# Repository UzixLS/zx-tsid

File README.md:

## ZX-TSid
MOS SID sound card for ZX Spectrum edge connector (ZX-BUS).

PCB is compatible with SID 6581 and 8580, but also contains integrated SwinSID emulator.

SID accessible via #xxCF port, where xx - SID's register number.

You may connect your ZX Spectrum audio output to second 3.5mm jack and it will be mixed in sound card output signal.

NOTE: +12V/+9V voltage is strictly required for SID, your ZX Spectrum or clone must provide it on the edge connector.

### Changelog & current status
* Rev.A - initial release with SID, AY and Covox. [Errata](pcb/rev.A/ERRATA.txt).
* Rev.B - abandoned. Files kept for historical reason.
* Rev.C - removed AY and Covox. Added SwinSID emulator. PCB is vertical oriented now.
* Rev.D - improved signal-noise ratio. Fixed read from SID chip.

TODO:
* Check with 8580 SID chip;
* Further improve signal-noise ratio.

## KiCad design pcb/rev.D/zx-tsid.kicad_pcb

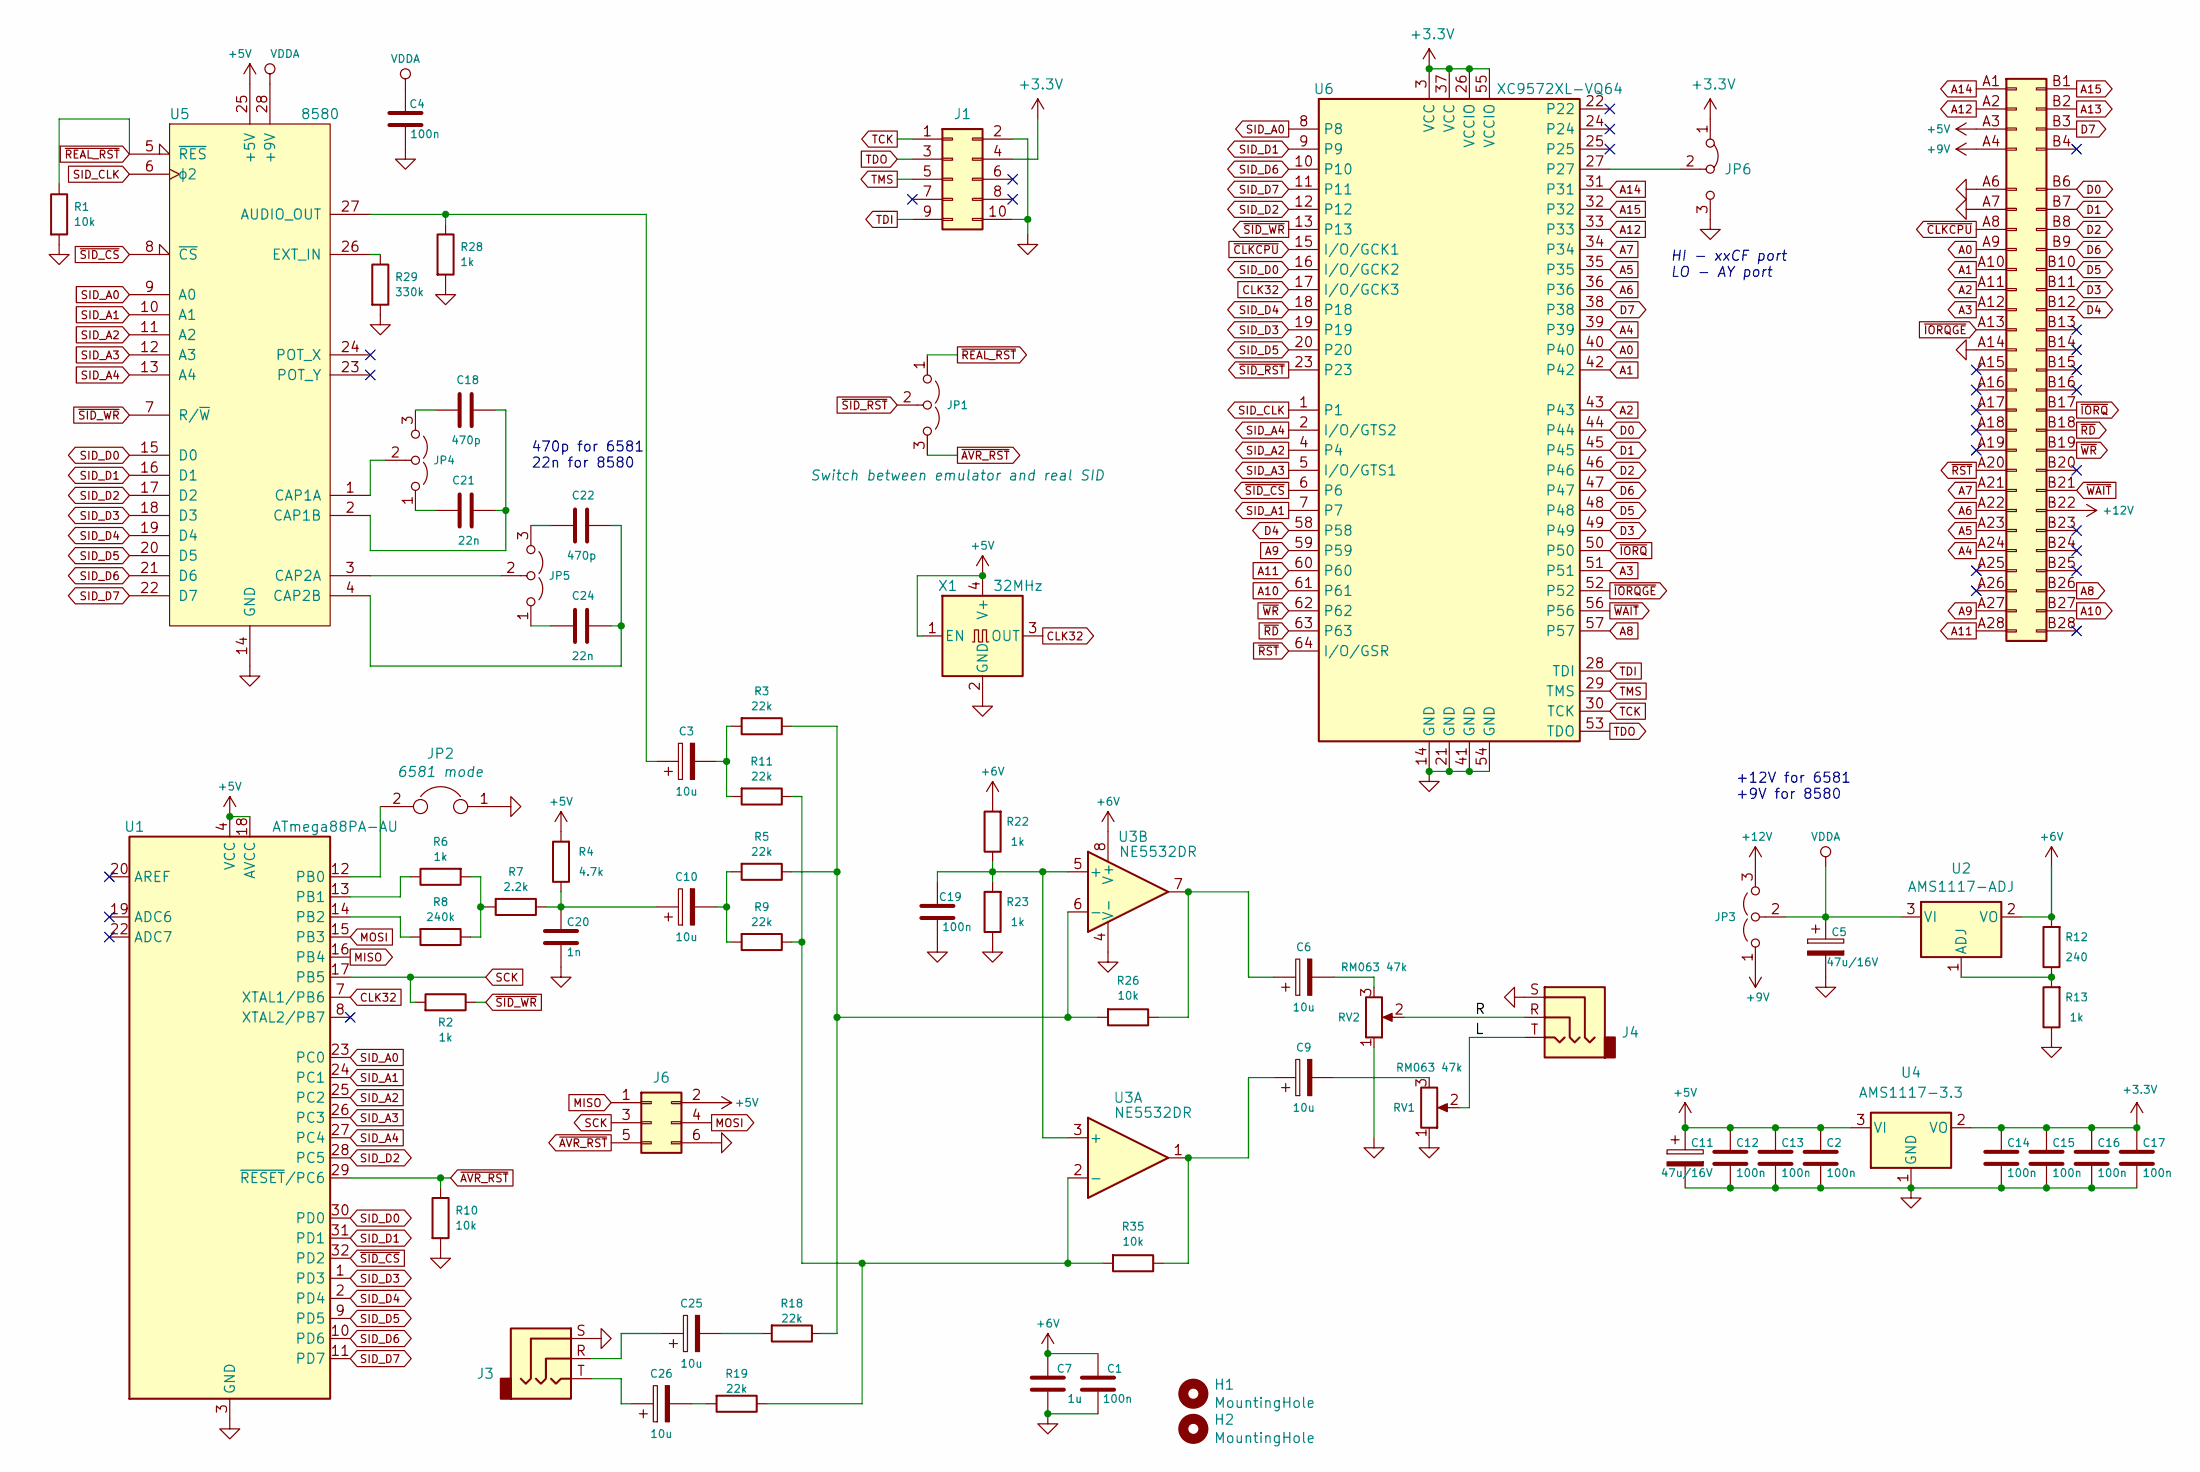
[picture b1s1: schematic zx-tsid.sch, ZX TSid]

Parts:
C1, C2, C4, C12, C13, C14, C15, C16, C17, C19: 100n; C_0603_1608Metric_Pad1.05x0.95mm_HandSolder
C3, C6, C9, C10, C25, C26: 10u; CP_EIA-3216-18_Kemet-A_Pad1.58x1.35mm_HandSolder
C5, C11: 47u/16V; CP_EIA-6032-28_Kemet-C_Pad2.25x2.35mm_HandSolder
C7: 1u; C_0805_2012Metric_Pad1.15x1.40mm_HandSolder
C18, C22: 470p; C_Rect_L7.0mm_W4.5mm_P5.00mm
C20: 1n; C_0603_1608Metric_Pad1.05x0.95mm_HandSolder
C21, C24: 22n; C_Rect_L7.0mm_W2.5mm_P5.00mm
H1, H2: MountingHole; MountingHole_3.2mm_M3
J1: Conn_02x05_Odd_Even; PinHeader_2x05_P2.54mm_Vertical_SMD
J2: zx_edge; Spectrum_Edge_Connector
J3, J4: PJ-313
J6: Conn_02x03_Odd_Even; PinHeader_2x03_P2.54mm_Vertical_SMD
JP1, JP3, JP4, JP5: Jumper_3_Open; PinHeader_1x03_P2.54mm_Vertical
JP2: Jumper; PinHeader_1x02_P2.54mm_Vertical
JP6: Jumper_3_Bridged12; SolderJumper-3_P1.3mm_Bridged12_RoundedPad1.0x1.5mm_NumberL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
R1, R10, R26, R35: 10k; R_0603_1608Metric_Pad1.05x0.95mm_HandSolder
R2, R6, R13, R22, R23, R28: 1k; R_0603_1608Metric_Pad1.05x0.95mm_HandSolder
R3, R5, R9, R11, R18, R19: 22k; R_0603_1608Metric_Pad1.05x0.95mm_HandSolder
R4: 4.7k; R_0603_1608Metric_Pad1.05x0.95mm_HandSolder
R7: 2.2k; R_0603_1608Metric_Pad1.05x0.95mm_HandSolder
R8: 240k; R_0603_1608Metric_Pad1.05x0.95mm_HandSolder
R12: 240; R_0603_1608Metric_Pad1.05x0.95mm_HandSolder
R29: 330k; R_0603_1608Metric_Pad1.05x0.95mm_HandSolder
RV1, RV2: RM063 47k; Potentiometer_Runtron_RM-063_Horizontal
U1: ATmega88PA-AU; TQFP-32_7x7mm_P0.8mm
U2: AMS1117-ADJ; SOT-223-3_TabPin2
U3: NE5532DR; SOIC-8_3.9x4.9mm_P1.27mm
U4: AMS1117-3.3; SOT-223-3_TabPin2
U5: 8580; DIP-28_W15.24mm_Socket
U6: XC9572XL-VQ64; TQFP-64_10x10mm_P0.5mm
X1: 32MHz; Oscillator_SMD_EuroQuartz_XO91-4Pin_7.0x5.0mm_HandSoldering

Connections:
+3V3: C14.1, C15.1, C16.1, C17.1, J1.4, JP6.1 (A), U4.2 (VO), U6.3 (VCC), U6.26 (VCCIO), U6.37 (VCC), U6.55 (VCCIO)
+5V: C2.1, C11.1, C12.1, C13.1, J2.A3 (Pin_a3), J6.2, R4.2, U1.4 (VCC), U1.6 (VCC), U1.18 (AVCC), U4.3 (VI), U5.25 (+5V), X1.1 (EN), X1.4 (V+)
+6V: C1.2, C7.2, R12.2, R22.2, U2.2 (VO), U3.8 (V+)
+9V: J2.A4 (Pin_a4), JP3.1 (A)
+12V: J2.B22 (Pin_b22), JP3.3 (B)
/L: J4.T, RV1.2
/R: J4.R, RV2.2
A0: J2.A9 (Pin_a9), U6.40
A1: J2.A10 (Pin_a10), U6.42
A2: J2.A11 (Pin_a11), U6.43
A3: J2.A12 (Pin_a12), U6.51
A4: J2.A24 (Pin_a24), U6.39
A5: J2.A23 (Pin_a23), U6.35
A6: J2.A22 (Pin_a22), U6.36
A7: J2.A21 (Pin_a21), U6.34
A8: J2.B26 (Pin_b26), U6.57
A9: J2.A27 (Pin_a27), U6.59
A10: J2.B27 (Pin_b27), U6.61
A11: J2.A28 (Pin_a28), U6.60
A12: J2.A2 (Pin_a2), U6.33
A14: J2.A1 (Pin_a1), U6.31
A15: J2.B1 (Pin_b1), U6.32
CLK32: U1.7 (XTAL1/PB6), U6.17 (I/O/GCK3), X1.3 (OUT)
D0: J2.B6 (Pin_b6), U6.44
D1: J2.B7 (Pin_b7), U6.45
D2: J2.B8 (Pin_b8), U6.46
D3: J2.B11 (Pin_b11), U6.49
D4: J2.B12 (Pin_b12), U6.58
D5: J2.B10 (Pin_b10), U6.48
D6: J2.B9 (Pin_b9), U6.47
D7: J2.B3 (Pin_b3), U6.38
GND: C1.1, C2.2, C4.1, C5.2, C7.1, C11.2, C12.2, C13.2, C14.2, C15.2, C16.2, C17.2, C19.1, C20.2, J1.2, J1.10, J2.A6 (Pin_a6), J2.A7 (Pin_a7), J2.A14 (Pin_a14), J3.S, J4.S, J6.6, JP2.1, JP6.3 (B), R1.2, R10.2, R13.1, R23.1, R28.2, R29.2, RV1.1, RV2.1, U1.3 (GND), U1.5 (GND), U1.21 (GND), U3.4 (V-), U4.1 (GND), U5.14 (GND), U6.14 (GND), U6.21 (GND), U6.41 (GND), U6.54 (GND), X1.2 (GND)
MISO: J6.1, U1.16 (PB4)
MOSI: J6.4, U1.15 (PB3)
unnamed: C3.1, R28.1, U5.27 (AUDIO_OUT)
unnamed: C3.2, R3.2, R11.2
unnamed: C6.1, R26.1, U3.7
unnamed: C6.2, RV2.3
unnamed: C9.1, R35.1, U3.1
unnamed: C9.2, RV1.3
unnamed: C10.1, C20.1, R4.1, R7.1
unnamed: C10.2, R5.2, R9.2
unnamed: C18.1, C21.2, U5.2 (CAP1B)
unnamed: C18.2, JP4.3 (B)
unnamed: C19.2, R22.1, R23.2, U3.3 (+), U3.5 (+)
unnamed: C21.1, JP4.1 (A)
unnamed: C22.1, C24.1, U5.4 (CAP2B)
unnamed: C22.2, JP5.3 (B)
unnamed: C24.2, JP5.1 (A)
unnamed: C25.1, J3.R
unnamed: C25.2, R18.2
unnamed: C26.1, J3.T
unnamed: C26.2, R19.2
unnamed: JP2.2, U1.12 (PB0)
unnamed: JP4.2 (C), U5.1 (CAP1A)
unnamed: JP5.2 (C), U5.3 (CAP2A)
unnamed: JP6.2 (C), U6.27
unnamed: R6.1, U1.13 (PB1)
unnamed: R6.2, R7.2, R8.1
unnamed: R8.2, U1.14 (PB2)
unnamed: R9.1, R11.1, R19.1, R35.2, U3.2 (-)
unnamed: R12.1, R13.2, U2.1 (ADJ)
unnamed: R3.1, R5.1, R18.1, R26.2, U3.6 (-)
unnamed: R29.1, U5.26 (EXT_IN)
SCK: J6.3, R2.2, U1.17 (PB5)
SID_A0: U1.23 (PC0), U5.9 (A0), U6.8
SID_A1: U1.24 (PC1), U5.10 (A1), U6.7
SID_A2: U1.25 (PC2), U5.11 (A2), U6.4
SID_A3: U1.26 (PC3), U5.12 (A3), U6.5 (I/O/GTS1)
SID_A4: U1.27 (PC4), U5.13 (A4), U6.2 (I/O/GTS2)
SID_CLK: U5.6 (ϕ2), U6.1
SID_D0: U1.30 (PD0), U5.15 (D0), U6.16 (I/O/GCK2)
SID_D1: U1.31 (PD1), U5.16 (D1), U6.9
SID_D2: U1.28 (PC5), U5.17 (D2), U6.12
SID_D3: U1.1 (PD3), U5.18 (D3), U6.19
SID_D4: U1.2 (PD4), U5.19 (D4), U6.18
SID_D5: U1.9 (PD5), U5.20 (D5), U6.20
SID_D6: U1.10 (PD6), U5.21 (D6), U6.10
SID_D7: U1.11 (PD7), U5.22 (D7), U6.11
TCK: J1.1, U6.30 (TCK)
TDI: J1.9, U6.28 (TDI)
TDO: J1.3, U6.53 (TDO)
TMS: J1.5, U6.29 (TMS)
VDDA: C4.2, C5.1, JP3.2 (C), U2.3 (VI), U5.28 (+9V)
~AVR_RST: J6.5, JP1.3 (B), R10.1, U1.29 (~RESET~/PC6)
~CLKCPU: J2.A8 (Pin_a8), U6.15 (I/O/GCK1)
~IORQ: J2.B17 (Pin_b17), U6.50
~IORQGE: J2.A13 (Pin_a13), U6.52
~RD: J2.B18 (Pin_b18), U6.63
~REAL_RST: JP1.1 (A), R1.1, U5.5 (~RES)
~RST: J2.A20 (Pin_a20), U6.64 (I/O/GSR)
~SID_CS: U1.32 (PD2), U5.8 (~CS), U6.6
~SID_RST: JP1.2 (C), U6.23
~SID_WR: R2.1, U5.7 (R/~W), U6.13
~WAIT: J2.B21 (Pin_b21), U6.56
~WR: J2.B19 (Pin_b19), U6.62

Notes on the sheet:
470p for 6581 22n for 8580
HI - xxCF port LO - AY port
+12V for 6581 +9V for 8580

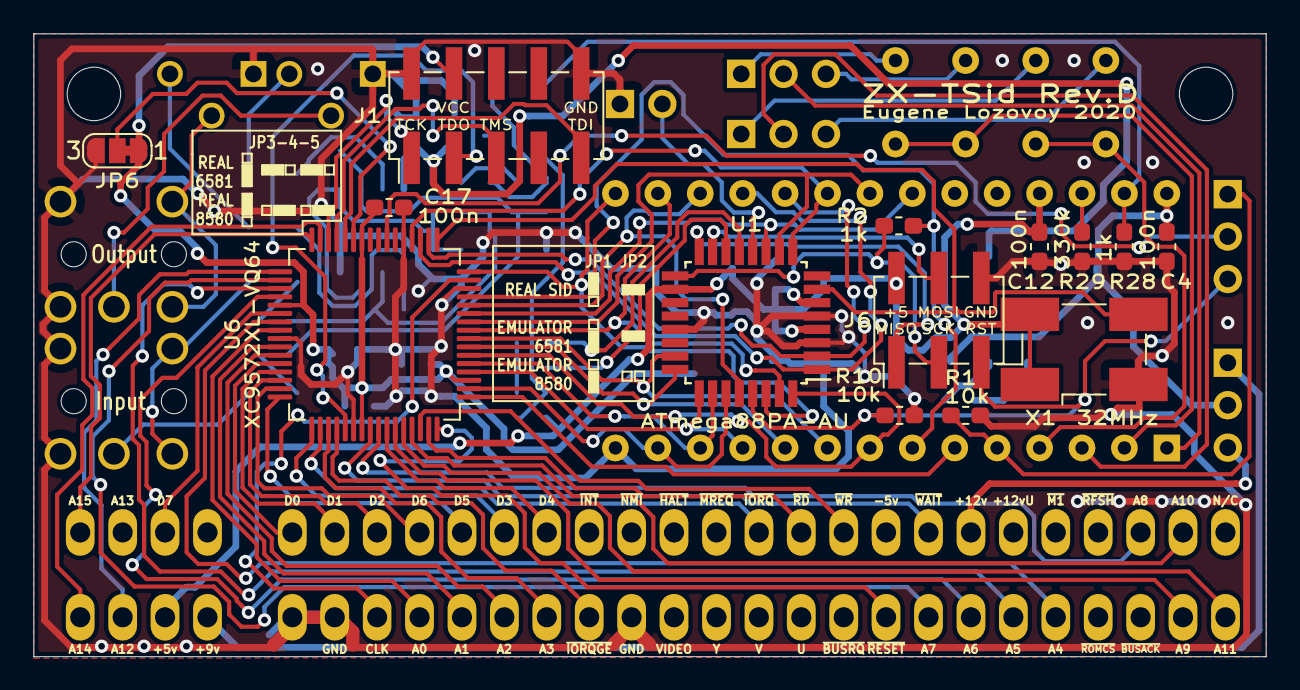
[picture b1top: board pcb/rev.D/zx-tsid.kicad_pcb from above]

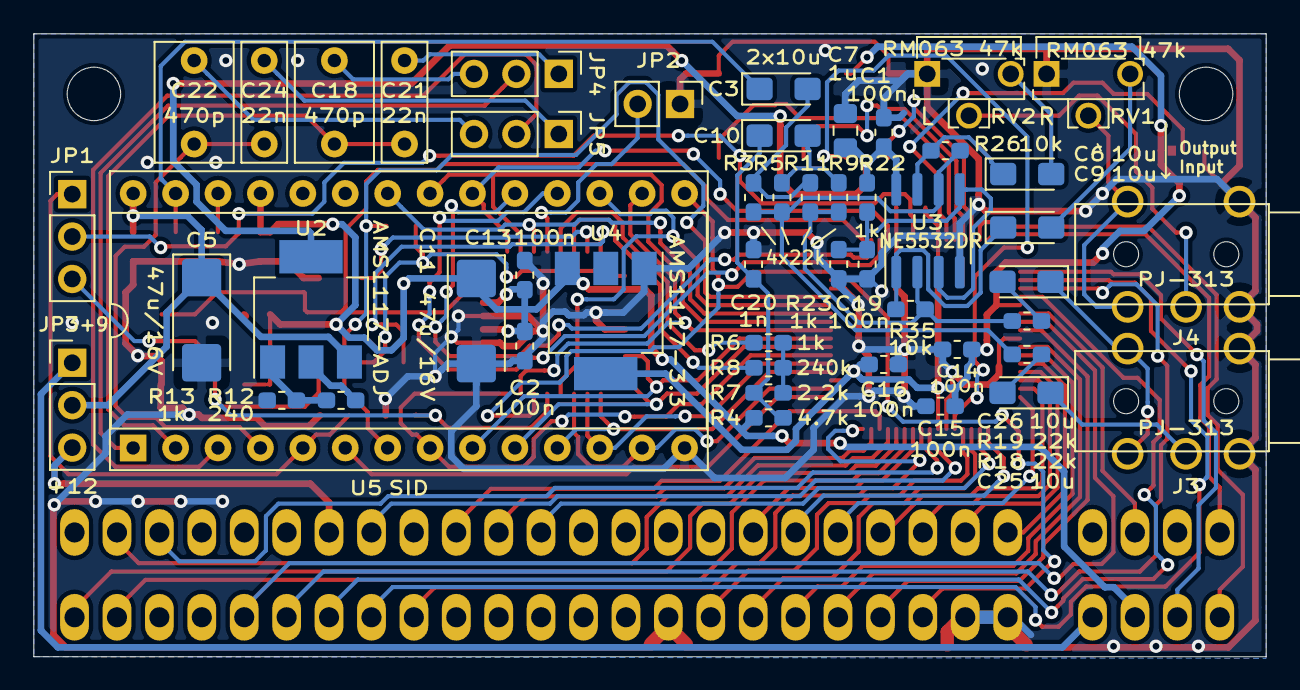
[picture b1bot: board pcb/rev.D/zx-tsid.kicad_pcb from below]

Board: 2 copper layers, 73.8 x 37.3 mm, 67 parts (52 on the bottom side), 96 nets.

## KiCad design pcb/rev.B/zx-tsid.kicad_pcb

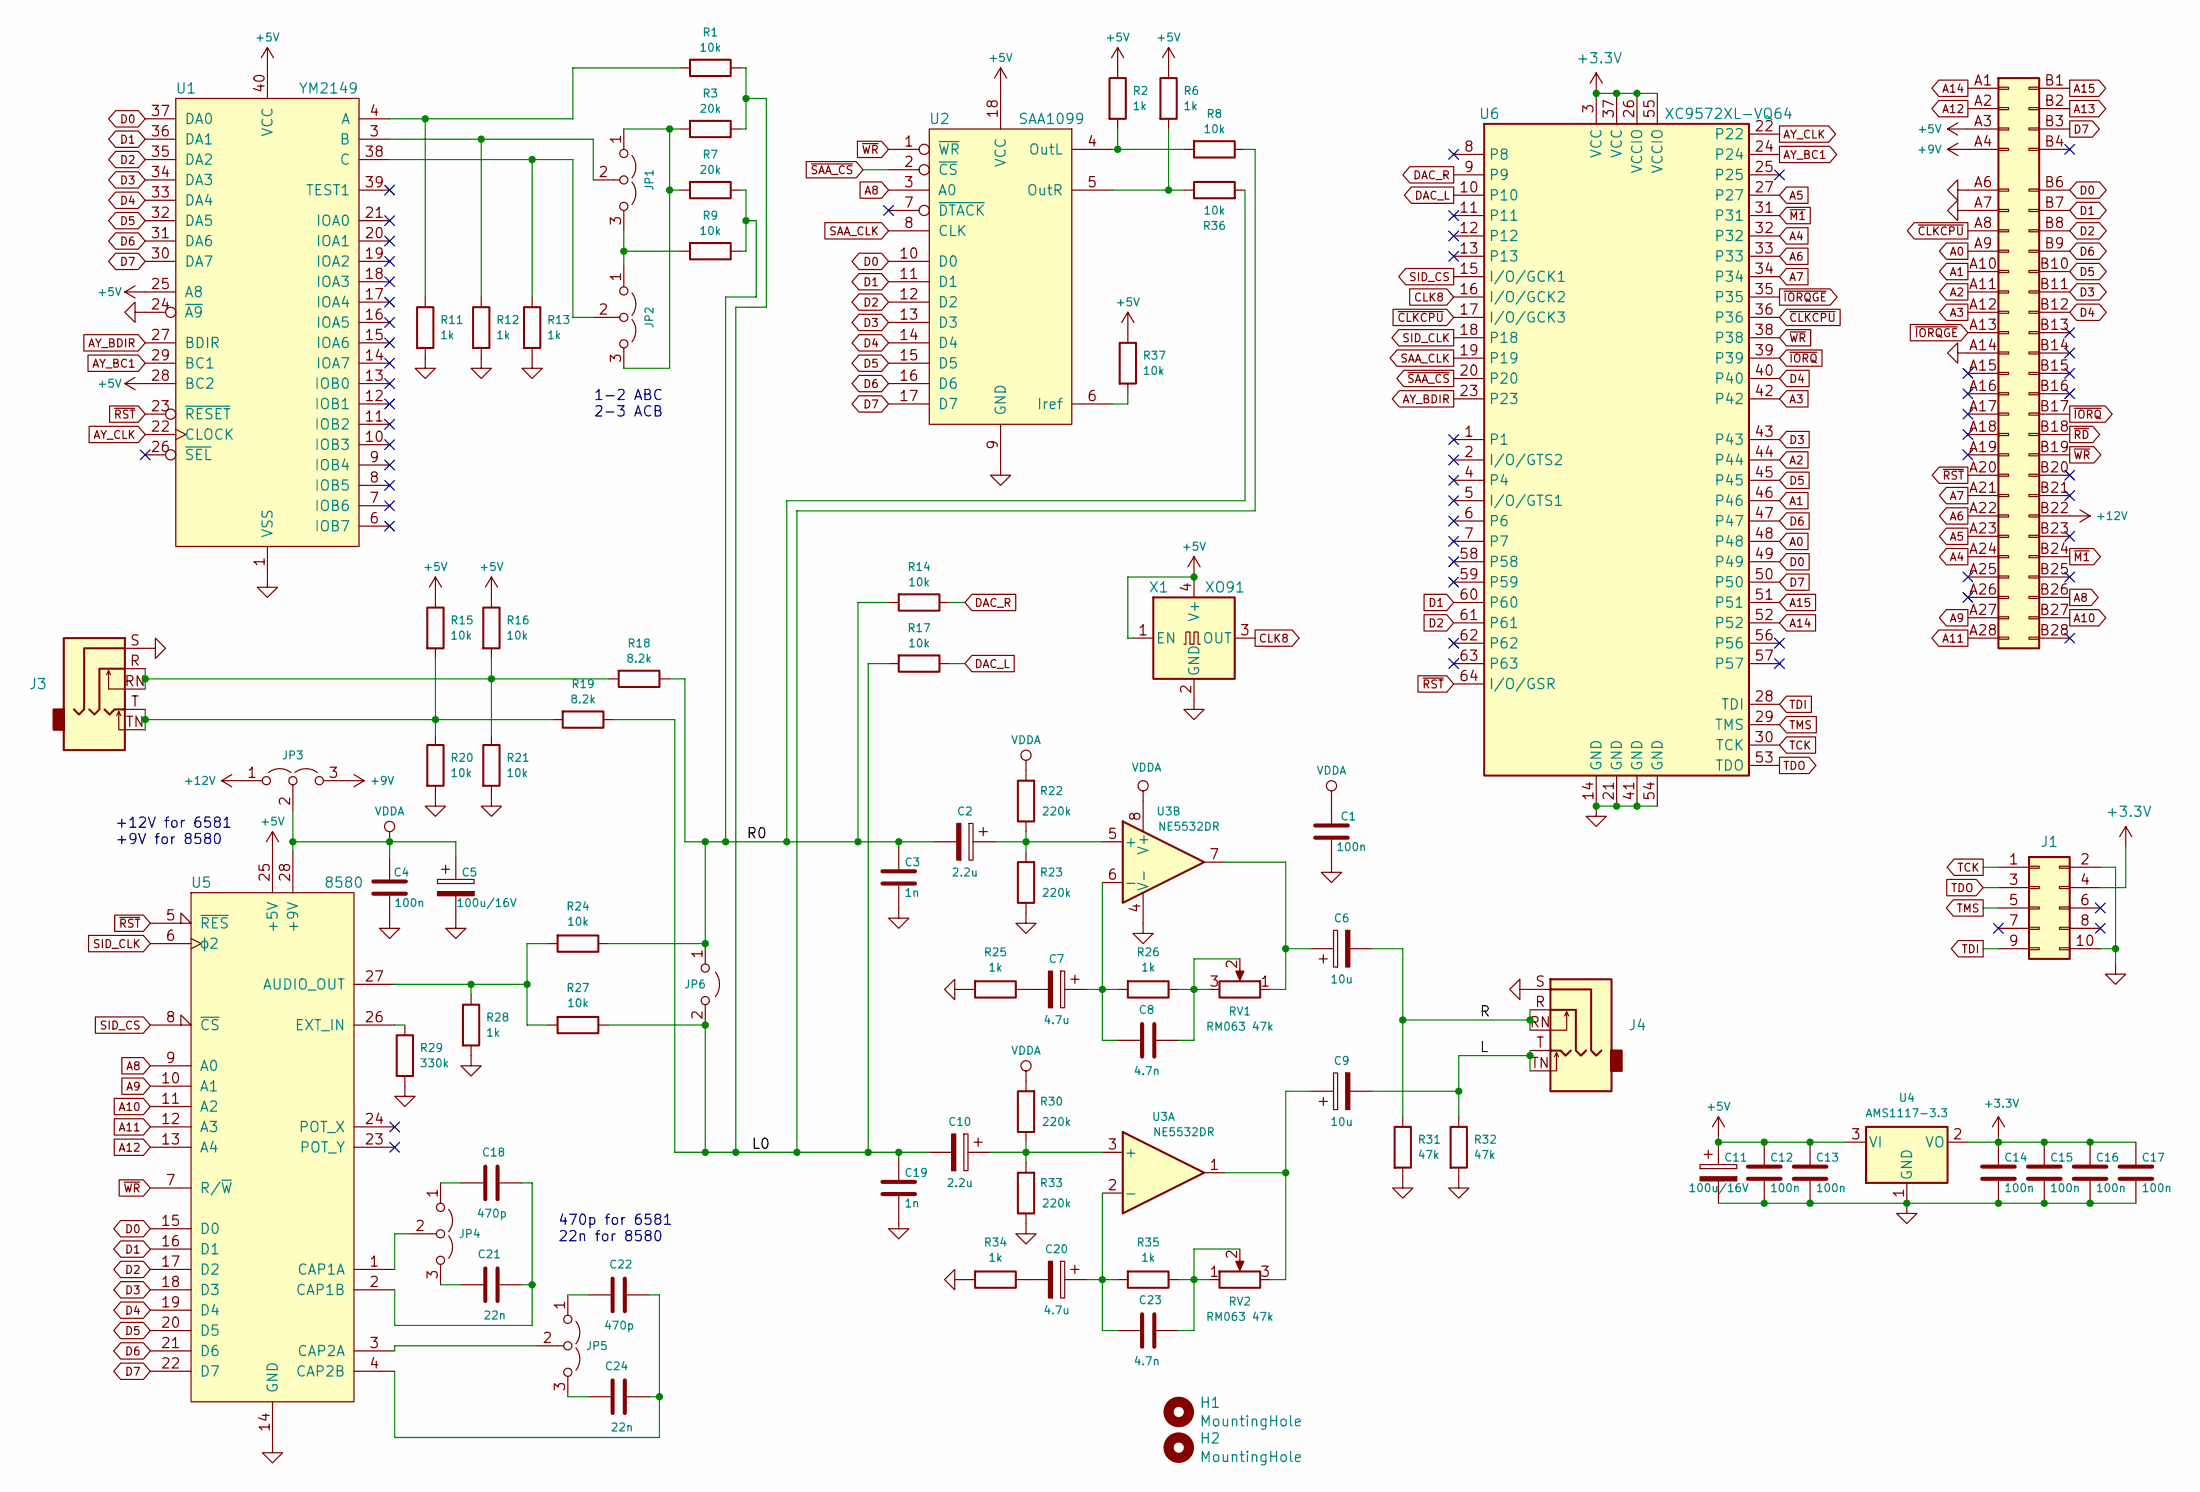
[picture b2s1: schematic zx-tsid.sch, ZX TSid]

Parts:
C1, C4, C12, C13, C14, C15, C16, C17: 100n; C_0603_1608Metric_Pad1.05x0.95mm_HandSolder
C2, C10: 2.2u; CP_EIA-3216-18_Kemet-A_Pad1.58x1.35mm_HandSolder
C3, C19: 1n; C_0603_1608Metric_Pad1.05x0.95mm_HandSolder
C5, C11: 100u/16V; CP_EIA-6032-28_Kemet-C_Pad2.25x2.35mm_HandSolder
C6, C9: 10u; CP_EIA-3216-18_Kemet-A_Pad1.58x1.35mm_HandSolder
C7, C20: 4.7u; CP_EIA-3216-18_Kemet-A_Pad1.58x1.35mm_HandSolder
C8, C23: 4.7n; C_0603_1608Metric_Pad1.05x0.95mm_HandSolder
C18, C22: 470p; C_Rect_L7.0mm_W4.5mm_P5.00mm
C21, C24: 22n; C_Rect_L7.0mm_W2.5mm_P5.00mm
H1, H2: MountingHole; MountingHole_3.2mm_M3
J1: Conn_02x05_Odd_Even; PinHeader_2x05_P2.54mm_Vertical_SMD
J2: zx_edge; ZX_CONN
J3, J4: PJ307
JP1, JP2, JP3, JP4, JP5: Jumper_3_Open; PinHeader_1x03_P2.54mm_Vertical
JP6: Jumper_2_Open; PinHeader_1x02_P2.54mm_Vertical
R1, R8, R9, R14, R15, R16, R17, R20, R21, R24, R27, R36, R37: 10k; R_0603_1608Metric_Pad1.05x0.95mm_HandSolder
R2, R6, R11, R12, R13, R25, R26, R28, R34, R35: 1k; R_0603_1608Metric_Pad1.05x0.95mm_HandSolder
R3, R7: 20k; R_0603_1608Metric_Pad1.05x0.95mm_HandSolder
R18, R19: 8.2k; R_0603_1608Metric_Pad1.05x0.95mm_HandSolder
R22, R23, R30, R33: 220k; R_0603_1608Metric_Pad1.05x0.95mm_HandSolder
R29: 330k; R_0603_1608Metric_Pad1.05x0.95mm_HandSolder
R31, R32: 47k; R_0603_1608Metric_Pad1.05x0.95mm_HandSolder
RV1, RV2: RM063 47k; Potentiometer_Runtron_RM-063_Horizontal
U1: YM2149; DIP-40_W15.24mm_Socket
U2: SAA1099; DIP-18_W7.62mm_Socket
U3: NE5532DR; SOIC-8_3.9x4.9mm_P1.27mm
U4: AMS1117-3.3; SOT-223-3_TabPin2
U5: 8580; DIP-28_W15.24mm_Socket
U6: XC9572XL-VQ64; TQFP-64_10x10mm_P0.5mm
X1: XO91; Oscillator_SMD_EuroQuartz_XO91-4Pin_7.0x5.0mm

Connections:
+3V3: C14.1, C15.1, C16.1, C17.1, J1.4, U4.2 (VO), U6.3 (VCC), U6.26 (VCCIO), U6.37 (VCC), U6.55 (VCCIO)
+5V: C11.1, C12.1, C13.1, J2.A3 (Pin_a3), R2.1, R6.1, R15.1, R16.1, R37.1, U1.25 (A8), U1.28 (BC2), U1.40 (VCC), U2.18 (VCC), U4.3 (VI), U5.25 (+5V), X1.1 (EN), X1.4 (V+)
+9V: J2.A4 (Pin_a4), JP3.3 (B)
+12V: J2.B22 (Pin_b22), JP3.1 (A)
/L: C9.2, J4.T, J4.TN, R32.1
/L0: C10.2, C19.1, JP6.2 (B), R1.1, R3.1, R8.1, R17.2, R19.1, R27.1
/R: C6.2, J4.R, J4.RN, R31.1
/R0: C2.2, C3.1, JP6.1 (A), R7.1, R9.1, R14.2, R18.1, R24.1, R36.2
A0: J2.A9 (Pin_a9), U6.48
A1: J2.A10 (Pin_a10), U6.46
A2: J2.A11 (Pin_a11), U6.44
A3: J2.A12 (Pin_a12), U6.42
A4: J2.A24 (Pin_a24), U6.32
A5: J2.A23 (Pin_a23), U6.27
A6: J2.A22 (Pin_a22), U6.33
A7: J2.A21 (Pin_a21), U6.34
A8: J2.B26 (Pin_b26), U2.3 (A0), U5.9 (A0)
A9: J2.A27 (Pin_a27), U5.10 (A1)
A10: J2.B27 (Pin_b27), U5.11 (A2)
A11: J2.A28 (Pin_a28), U5.12 (A3)
A12: J2.A2 (Pin_a2), U5.13 (A4)
A14: J2.A1 (Pin_a1), U6.52
A15: J2.B1 (Pin_b1), U6.51
AY_BC1: U1.29 (BC1), U6.24
AY_BDIR: U1.27 (BDIR), U6.23
AY_CLK: U1.22 (CLOCK), U6.22
CLK8: U6.16 (I/O/GCK2), X1.3 (OUT)
D0: J2.B6 (Pin_b6), U1.37 (DA0), U2.10 (D0), U5.15 (D0), U6.49
D1: J2.B7 (Pin_b7), U1.36 (DA1), U2.11 (D1), U5.16 (D1), U6.60
D2: J2.B8 (Pin_b8), U1.35 (DA2), U2.12 (D2), U5.17 (D2), U6.61
D3: J2.B11 (Pin_b11), U1.34 (DA3), U2.13 (D3), U5.18 (D3), U6.43
D4: J2.B12 (Pin_b12), U1.33 (DA4), U2.14 (D4), U5.19 (D4), U6.40
D5: J2.B10 (Pin_b10), U1.32 (DA5), U2.15 (D5), U5.20 (D5), U6.45
D6: J2.B9 (Pin_b9), U1.31 (DA6), U2.16 (D6), U5.21 (D6), U6.47
D7: J2.B3 (Pin_b3), U1.30 (DA7), U2.17 (D7), U5.22 (D7), U6.50
DAC_L: R17.1, U6.10
DAC_R: R14.1, U6.9
GND: C1.1, C3.2, C4.1, C5.2, C11.2, C12.2, C13.2, C14.2, C15.2, C16.2, C17.2, C19.2, J1.2, J1.10, J2.A6 (Pin_a6), J2.A7 (Pin_a7), J2.A14 (Pin_a14), J3.S, J4.S, R11.2, R12.2, R13.2, R20.2, R21.2, R23.1, R25.2, R28.2, R29.2, R31.2, R32.2, R33.1, R34.2, U1.1 (VSS), U1.24 (~A9~), U2.9 (GND), U3.4 (V-), U4.1 (GND), U5.14 (GND), U6.14 (GND), U6.21 (GND), U6.41 (GND), U6.54 (GND), X1.2 (GND)
unnamed: C2.1, R22.1, R23.2, U3.5 (+)
unnamed: C6.1, RV1.1, U3.7
unnamed: C7.1, C8.2, R26.2, U3.6 (-)
unnamed: C7.2, R25.1
unnamed: C8.1, R26.1, RV1.2, RV1.3
unnamed: C9.1, RV2.3, U3.1
unnamed: C10.1, R30.1, R33.2, U3.3 (+)
unnamed: C18.1, C21.2, U5.2 (CAP1B)
unnamed: C18.2, JP4.1 (A)
unnamed: C20.1, C23.2, R35.2, U3.2 (-)
unnamed: C20.2, R34.1
unnamed: C21.1, JP4.3 (B)
unnamed: C22.1, C24.2, U5.4 (CAP2B)
unnamed: C22.2, JP5.1 (A)
unnamed: C23.1, R35.1, RV2.1, RV2.2
unnamed: C24.1, JP5.3 (B)
unnamed: J3.R, J3.RN, R16.2, R18.2, R21.1
unnamed: J3.T, J3.TN, R15.2, R19.2, R20.1
unnamed: JP1.1 (A), JP2.3 (B), R3.2, R7.2
unnamed: JP1.2 (C), R12.1, U1.3 (B)
unnamed: JP1.3 (B), JP2.1 (A), R9.2
unnamed: JP2.2 (C), R13.1, U1.38 (C)
unnamed: JP4.2 (C), U5.1 (CAP1A)
unnamed: JP5.2 (C), U5.3 (CAP2A)
unnamed: R1.2, R11.1, U1.4 (A)
unnamed: R2.2, R8.2, U2.4 (OutL)
unnamed: R24.2, R27.2, R28.1, U5.27 (AUDIO_OUT)
unnamed: R29.1, U5.26 (EXT_IN)
unnamed: R6.2, R36.1, U2.5 (OutR)
unnamed: R37.2, U2.6 (Iref)
SAA_CLK: U2.8 (CLK), U6.19
SID_CLK: U5.6 (ϕ2), U6.18
SID_CS: U5.8 (~CS), U6.15 (I/O/GCK1)
TCK: J1.1, U6.30 (TCK)
TDI: J1.9, U6.28 (TDI)
TDO: J1.3, U6.53 (TDO)
TMS: J1.5, U6.29 (TMS)
VDDA: C1.2, C4.2, C5.1, JP3.2 (C), R22.2, R30.2, U3.8 (V+), U5.28 (+9V)
~CLKCPU: J2.A8 (Pin_a8), U6.17 (I/O/GCK3), U6.36
~IORQ: J2.B17 (Pin_b17), U6.39
~IORQGE: J2.A13 (Pin_a13), U6.35
~M1: J2.B24 (Pin_b24), U6.31
~RST: J2.A20 (Pin_a20), U1.23 (~RESET~), U5.5 (~RES), U6.64 (I/O/GSR)
~SAA_CS: U2.2 (~CS), U6.20
~WR: J2.B19 (Pin_b19), U2.1 (~WR), U5.7 (R/~W), U6.38

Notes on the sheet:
470p for 6581 22n for 8580
+12V for 6581 +9V for 8580
1-2 ABC 2-3 ACB

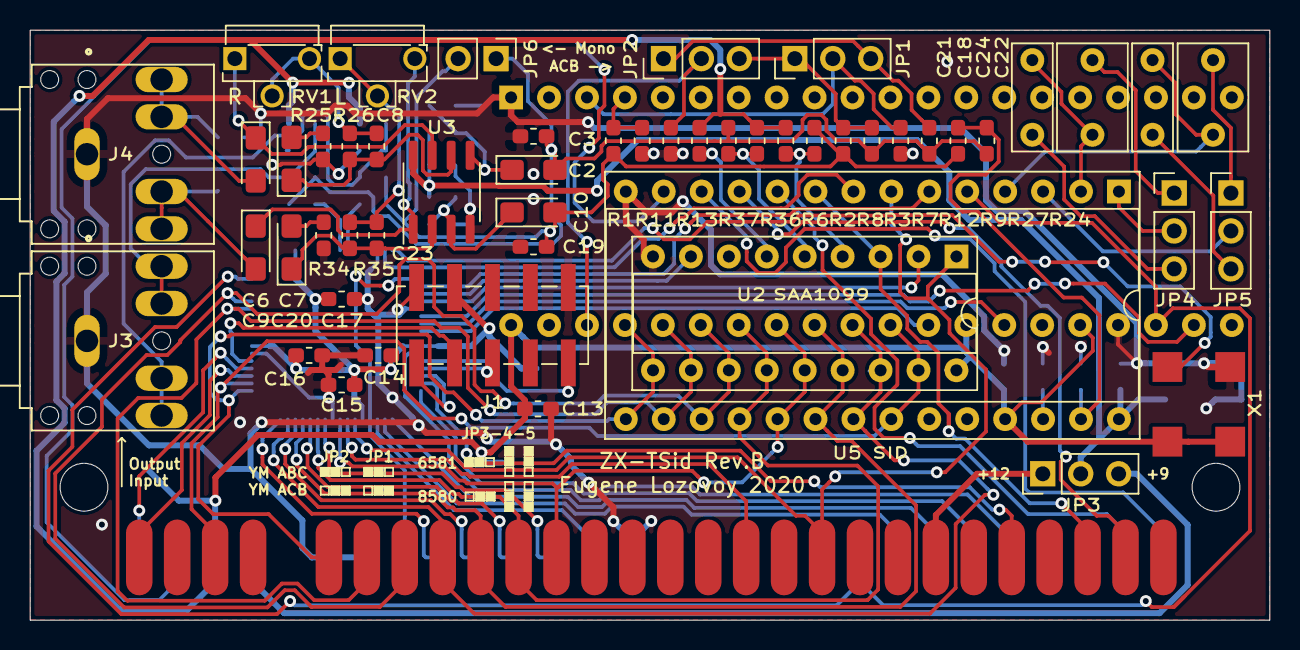
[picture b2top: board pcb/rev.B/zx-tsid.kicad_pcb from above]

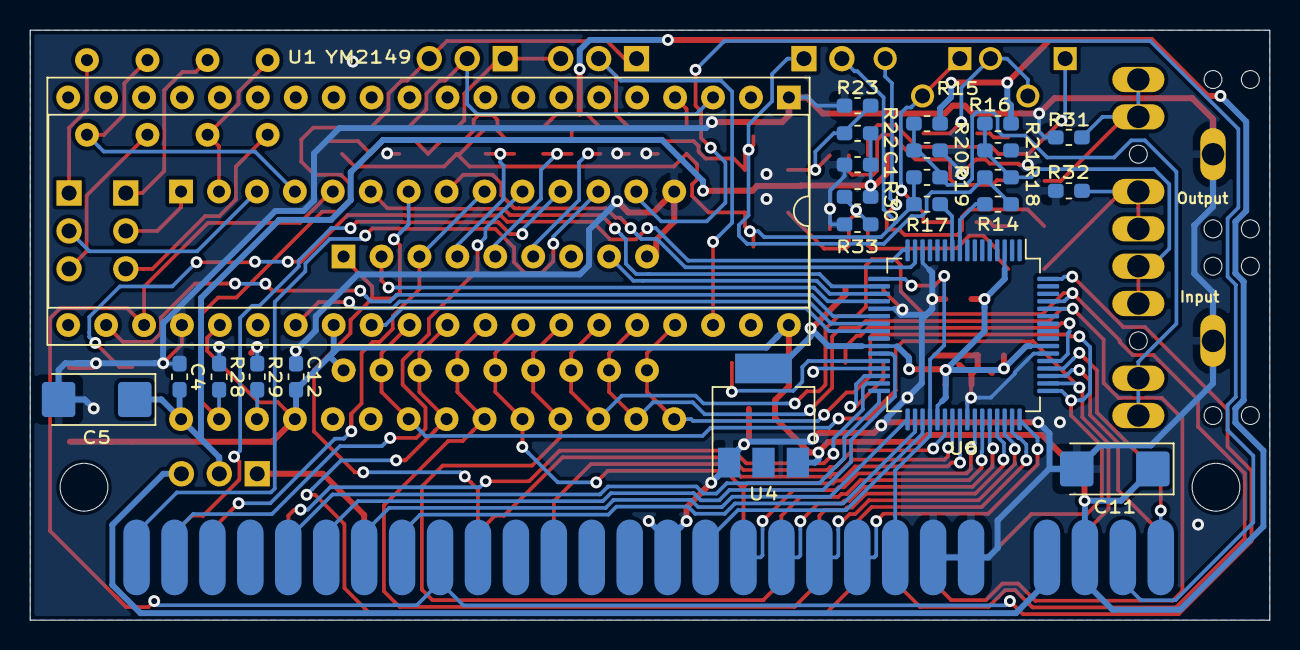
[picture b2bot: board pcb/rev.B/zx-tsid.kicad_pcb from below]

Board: 2 copper layers, 83.0 x 39.5 mm, 79 parts (24 on the bottom side), 83 nets.

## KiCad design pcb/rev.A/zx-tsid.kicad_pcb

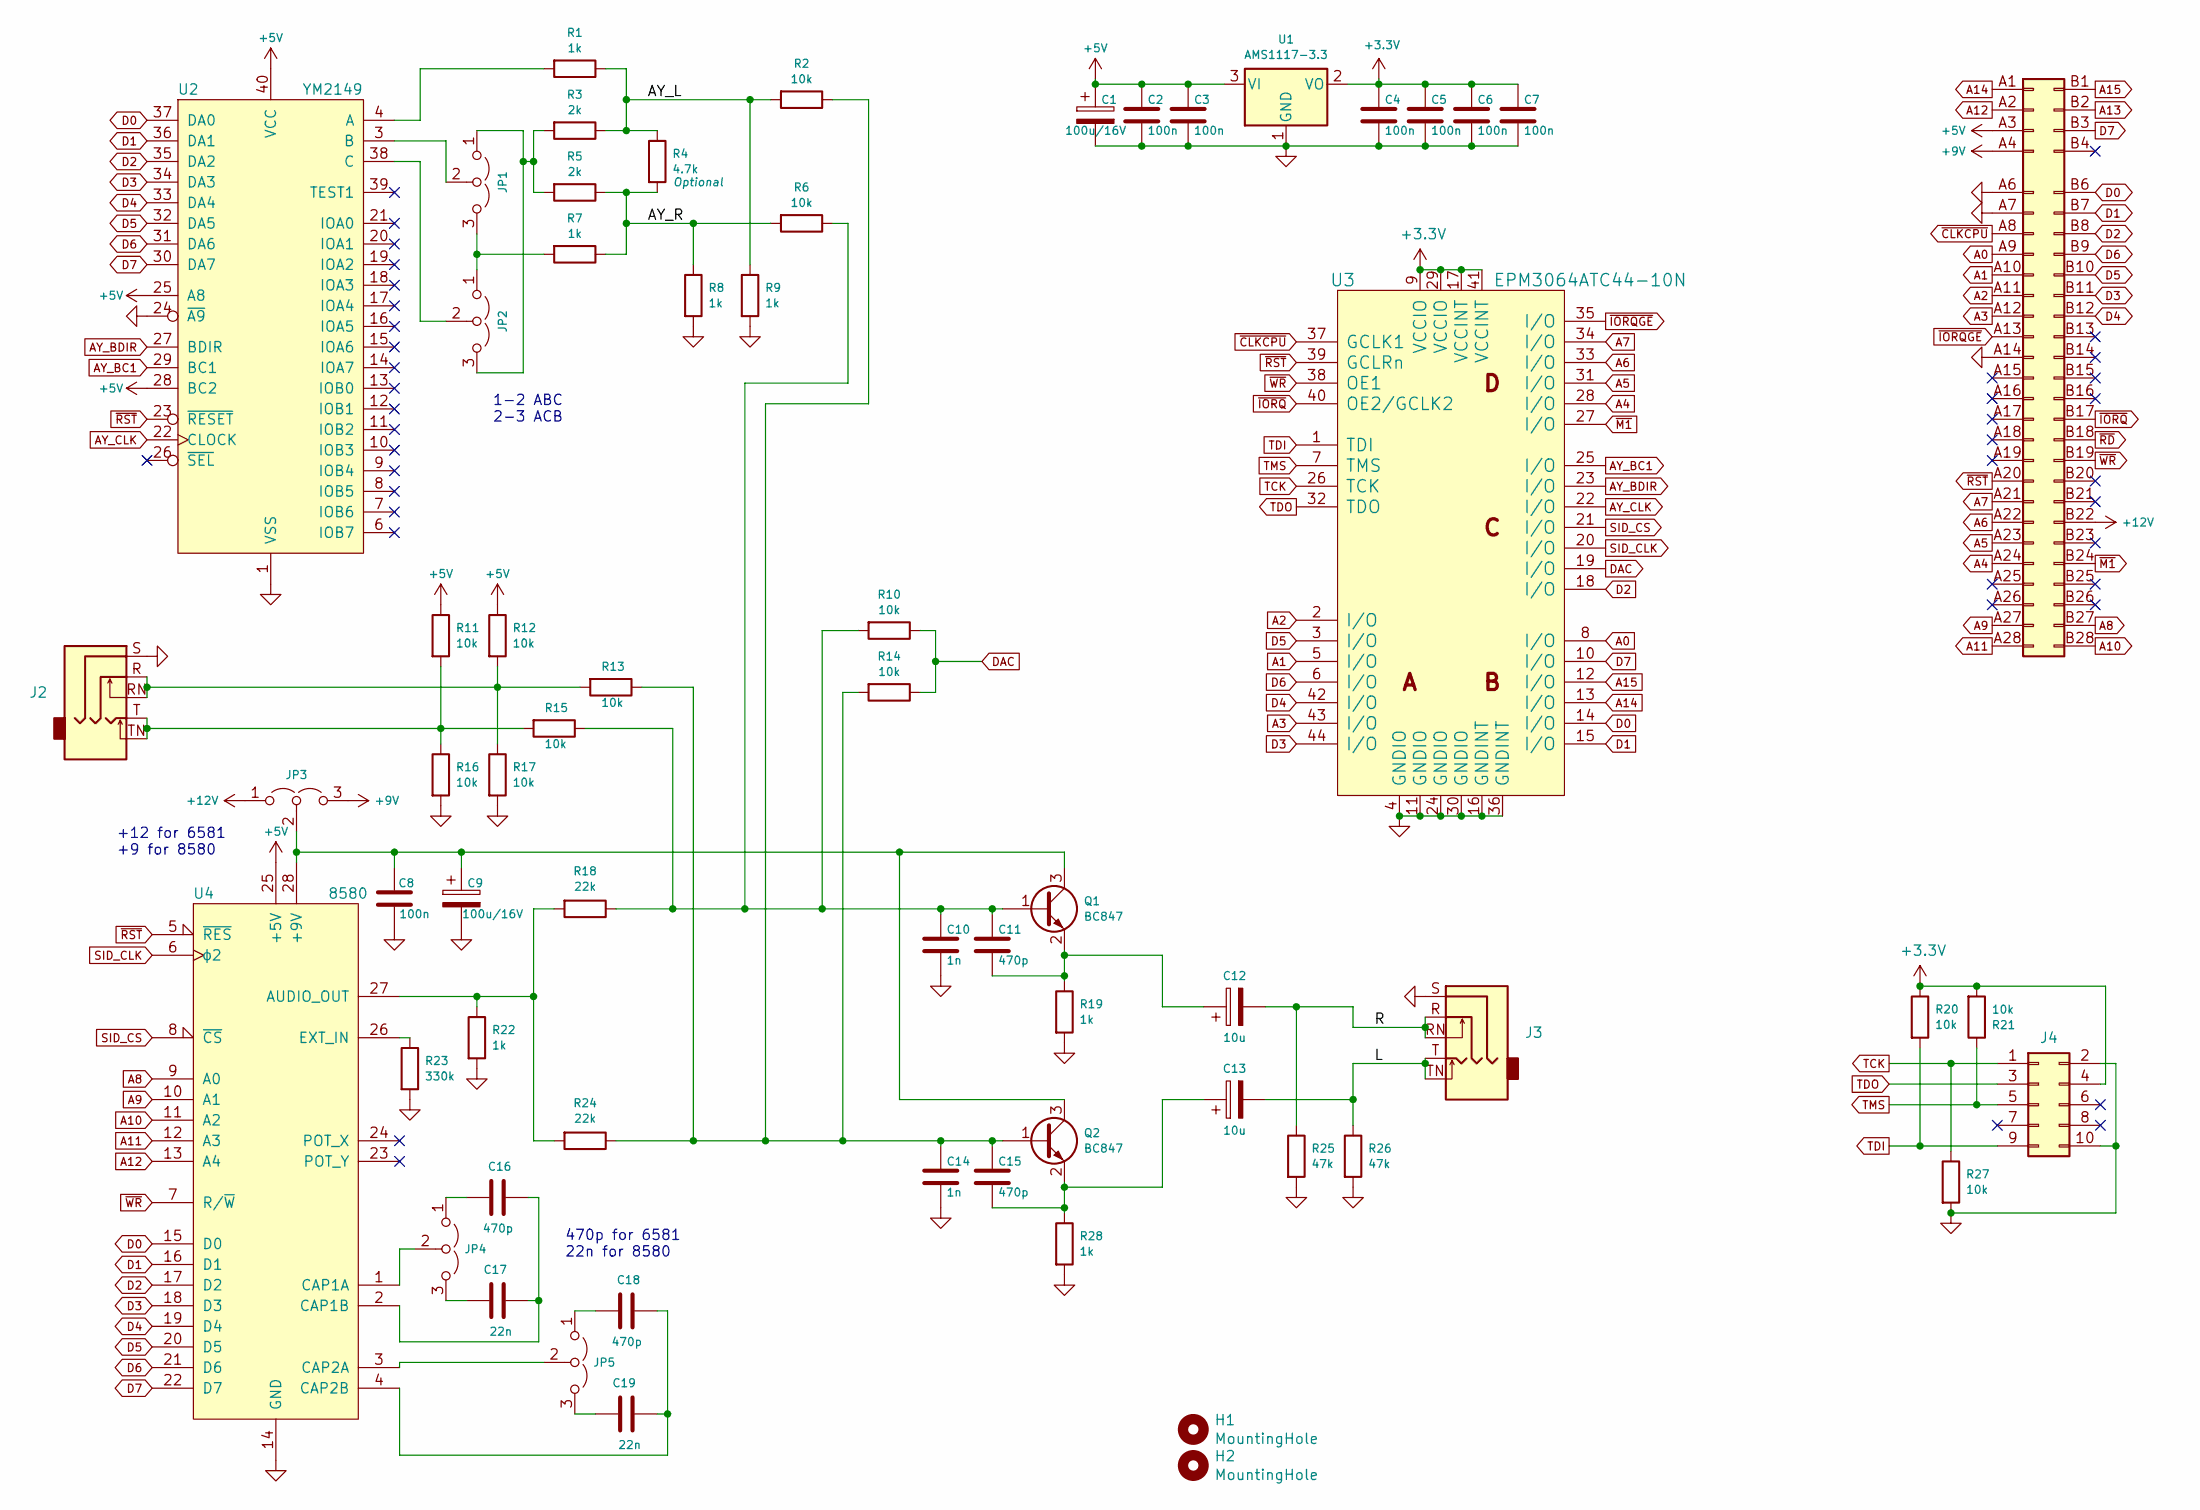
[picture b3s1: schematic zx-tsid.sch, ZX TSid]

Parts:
C1, C9: 100u/16V; CP_EIA-6032-15_Kemet-U_Pad2.25x2.35mm_HandSolder
C2, C3, C4, C5, C6, C7, C8: 100n; C_0603_1608Metric_Pad1.05x0.95mm_HandSolder
C10, C14: 1n; C_0603_1608Metric_Pad1.05x0.95mm_HandSolder
C11, C15: 470p; C_0603_1608Metric_Pad1.05x0.95mm_HandSolder
C12, C13: 10u; CP_Elec_6.3x5.4
C16, C18: 470p; C_Rect_L7.0mm_W4.5mm_P5.00mm
C17, C19: 22n; C_Rect_L7.0mm_W2.5mm_P5.00mm
H1, H2: MountingHole; MountingHole_3.2mm_M3
J1: zx_edge; ZX_CONN
J2, J3: PJ307; SWITCHCRAFT_35RAPC4BHN2
J4: Conn_02x05_Odd_Even; PinHeader_2x05_P2.54mm_Vertical_SMD
JP1, JP2, JP3, JP4, JP5: Jumper_3_Open; PinHeader_1x03_P2.54mm_Vertical
Q1, Q2: BC847; SOT-23_Handsoldering
R1, R7, R8, R9, R19, R22, R28: 1k; R_0603_1608Metric_Pad1.05x0.95mm_HandSolder
R2, R6, R10, R11, R12, R13, R14, R15, R16, R17, R20, R21, R27: 10k; R_0603_1608Metric_Pad1.05x0.95mm_HandSolder
R3, R5: 2k; R_0603_1608Metric_Pad1.05x0.95mm_HandSolder
R4: 4.7k; R_0603_1608Metric_Pad1.05x0.95mm_HandSolder
R18, R24: 22k; R_0603_1608Metric_Pad1.05x0.95mm_HandSolder
R23: 330k; R_0603_1608Metric_Pad1.05x0.95mm_HandSolder
R25, R26: 47k; R_0603_1608Metric_Pad1.05x0.95mm_HandSolder
U1: AMS1117-3.3; SOT-223-3_TabPin2
U2: YM2149; DIP-40_W15.24mm_Socket
U3: EPM3064ATC44-10N; QFP80P1200X1200X120-44N
U4: 8580; DIP-28_W15.24mm_Socket

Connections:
+3V3: C4.1, C5.1, C6.1, C7.1, J4.4, R20.1, R21.2, U1.2 (VO), U3.9 (VCCIO), U3.17 (VCCINT), U3.29 (VCCIO), U3.41 (VCCINT)
+5V: C1.1, C2.1, C3.1, J1.A3 (Pin_a3), R11.1, R12.1, U1.3 (VI), U2.25 (A8), U2.28 (BC2), U2.40 (VCC), U4.25 (+5V)
+9V: J1.A4 (Pin_a4), JP3.3 (B)
+12V: J1.B22 (Pin_b22), JP3.1 (A)
/AY_L: R1.1, R2.2, R3.1, R4.1, R9.1
/AY_R: R4.2, R5.1, R6.2, R7.1, R8.1
/L: C13.2, J3.T, J3.TN, R26.1
/R: C12.2, J3.R, J3.RN, R25.1
A0: J1.A9 (Pin_a9), U3.8 (I/O)
A1: J1.A10 (Pin_a10), U3.5 (I/O)
A2: J1.A11 (Pin_a11), U3.2 (I/O)
A3: J1.A12 (Pin_a12), U3.43 (I/O)
A4: J1.A24 (Pin_a24), U3.28 (I/O)
A5: J1.A23 (Pin_a23), U3.31 (I/O)
A6: J1.A22 (Pin_a22), U3.33 (I/O)
A7: J1.A21 (Pin_a21), U3.34 (I/O)
A8: J1.B27 (Pin_b27), U4.9 (A0)
A9: J1.A27 (Pin_a27), U4.10 (A1)
A10: J1.B28 (Pin_b28), U4.11 (A2)
A11: J1.A28 (Pin_a28), U4.12 (A3)
A12: J1.A2 (Pin_a2), U4.13 (A4)
A14: J1.A1 (Pin_a1), U3.13 (I/O)
A15: J1.B1 (Pin_b1), U3.12 (I/O)
AY_BC1: U2.29 (BC1), U3.25 (I/O)
AY_BDIR: U2.27 (BDIR), U3.23 (I/O)
AY_CLK: U2.22 (CLOCK), U3.22 (I/O)
D0: J1.B6 (Pin_b6), U2.37 (DA0), U3.14 (I/O), U4.15 (D0)
D1: J1.B7 (Pin_b7), U2.36 (DA1), U3.15 (I/O), U4.16 (D1)
D2: J1.B8 (Pin_b8), U2.35 (DA2), U3.18 (I/O), U4.17 (D2)
D3: J1.B11 (Pin_b11), U2.34 (DA3), U3.44 (I/O), U4.18 (D3)
D4: J1.B12 (Pin_b12), U2.33 (DA4), U3.42 (I/O), U4.19 (D4)
D5: J1.B10 (Pin_b10), U2.32 (DA5), U3.3 (I/O), U4.20 (D5)
D6: J1.B9 (Pin_b9), U2.31 (DA6), U3.6 (I/O), U4.21 (D6)
D7: J1.B3 (Pin_b3), U2.30 (DA7), U3.10 (I/O), U4.22 (D7)
DAC: R10.1, R14.1, U3.19 (I/O)
GND: C1.2, C2.2, C3.2, C4.2, C5.2, C6.2, C7.2, C8.1, C9.2, C10.2, C14.2, J1.A6 (Pin_a6), J1.A7 (Pin_a7), J1.A14 (Pin_a14), J2.S, J3.S, J4.2, J4.10, R8.2, R9.2, R16.2, R17.2, R19.2, R22.2, R23.2, R25.2, R26.2, R27.2, R28.2, U1.1 (GND), U2.1 (VSS), U2.24 (~A9~), U3.4 (GNDIO), U3.11 (GNDIO), U3.16 (GNDINT), U3.24 (GNDIO), U3.30 (GNDIO), U3.36 (GNDINT), U4.14 (GND)
unnamed: C8.2, C9.1, JP3.2 (C), Q1.3 (C), Q2.3 (C), U4.28 (+9V)
unnamed: C10.1, C11.1, Q1.1 (B), R6.1, R10.2, R15.1, R18.1
unnamed: C11.2, C12.1, Q1.2 (E), R19.1
unnamed: C13.1, C15.2, Q2.2 (E), R28.1
unnamed: C14.1, C15.1, Q2.1 (B), R2.1, R13.1, R14.2, R24.1
unnamed: C16.1, C17.2, U4.2 (CAP1B)
unnamed: C16.2, JP4.1 (A)
unnamed: C17.1, JP4.3 (B)
unnamed: C18.1, C19.2, U4.4 (CAP2B)
unnamed: C18.2, JP5.1 (A)
unnamed: C19.1, JP5.3 (B)
unnamed: J2.R, J2.RN, R12.2, R13.2, R17.1
unnamed: J2.T, J2.TN, R11.2, R15.2, R16.1
unnamed: JP1.1 (A), JP2.3 (B), R3.2, R5.2
unnamed: JP1.2 (C), U2.3 (B)
unnamed: JP1.3 (B), JP2.1 (A), R7.2
unnamed: JP2.2 (C), U2.38 (C)
unnamed: JP4.2 (C), U4.1 (CAP1A)
unnamed: JP5.2 (C), U4.3 (CAP2A)
unnamed: R1.2, U2.4 (A)
unnamed: R18.2, R22.1, R24.2, U4.27 (AUDIO_OUT)
unnamed: R23.1, U4.26 (EXT_IN)
SID_CLK: U3.20 (I/O), U4.6 (ϕ2)
SID_CS: U3.21 (I/O), U4.8 (~CS)
TCK: J4.1, R27.1, U3.26 (TCK)
TDI: J4.9, R20.2, U3.1 (TDI)
TDO: J4.3, U3.32 (TDO)
TMS: J4.5, R21.1, U3.7 (TMS)
~CLKCPU: J1.A8 (Pin_a8), U3.37 (GCLK1)
~IORQ: J1.B17 (Pin_b17), U3.40 (OE2/GCLK2)
~IORQGE: J1.A13 (Pin_a13), U3.35 (I/O)
~M1: J1.B24 (Pin_b24), U3.27 (I/O)
~RST: J1.A20 (Pin_a20), U2.23 (~RESET~), U3.39 (GCLRn), U4.5 (~RES)
~WR: J1.B19 (Pin_b19), U3.38 (OE1), U4.7 (R/~W)

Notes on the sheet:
470p for 6581 22n for 8580
+12 for 6581 +9 for 8580
1-2 ABC 2-3 ACB
